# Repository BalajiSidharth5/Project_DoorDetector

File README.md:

## Project_DoorDetector
# DOOR STATE DETECTOR
This project detects whether a door is open or closed using infrared reflection. It runs on two Adafruit HUZZAH32 boards.

# HOW IT WORKS
One HUZZAH32 sits at the door and reads the WWZMDiB 3 wire IR sensor. The sensor reflects IR off the door surface. When the door sits in front of the sensor, IR bounces back and the output reads one state. When the door swings open, the surface moves out of range and the output flips. A trim pot on the sensor sets the trigger distance.
The second HUZZAH32 acts as the receiver. It gets the door state and lights an LED to show open or closed.

# HARDWARE
- 2x Adafruit HUZZAH32
- WWZMDiB 3 wire IR sensor module
- 2x tactile pushbuttons, one on each HUZZAH32
- Status LED on each HUZZAH32, shows whether that board is awake
- LED on the receiver HUZZAH32, shows door open or closed state
- 220 ohm resistors for all LEDs
- 10k ohm resistors for both tactile buttons
- Rechargeable AA battery pack, wired directly to power and ground

# FIRMWARE
Button input is debounced in firmware on both boards.
Both boards run deep sleep to cut power draw. Each board wakes from deep sleep when you press its tactile button. The status LED on each board turns on when that board is awake and off when it drops back into deep sleep. This keeps both boards off when user does not need it. Utilized ESPnow library to communicate data between microcontrollers.

# POWER
The device runs on rechargeable AA cells instead of a lithium ion pack. Power and ground connect directly to the microcontroller with no charge circuit on board. Charging happens outside the device, in a standalone AA charger.

# STATUS
Breadboard prototype complete. PCB layout in progress in KiCad, targeting a compact 3D printed enclosure.

# NEXT STEPS
- Finish PCB layout in KiCad
- Design 3D printed enclosure around the board

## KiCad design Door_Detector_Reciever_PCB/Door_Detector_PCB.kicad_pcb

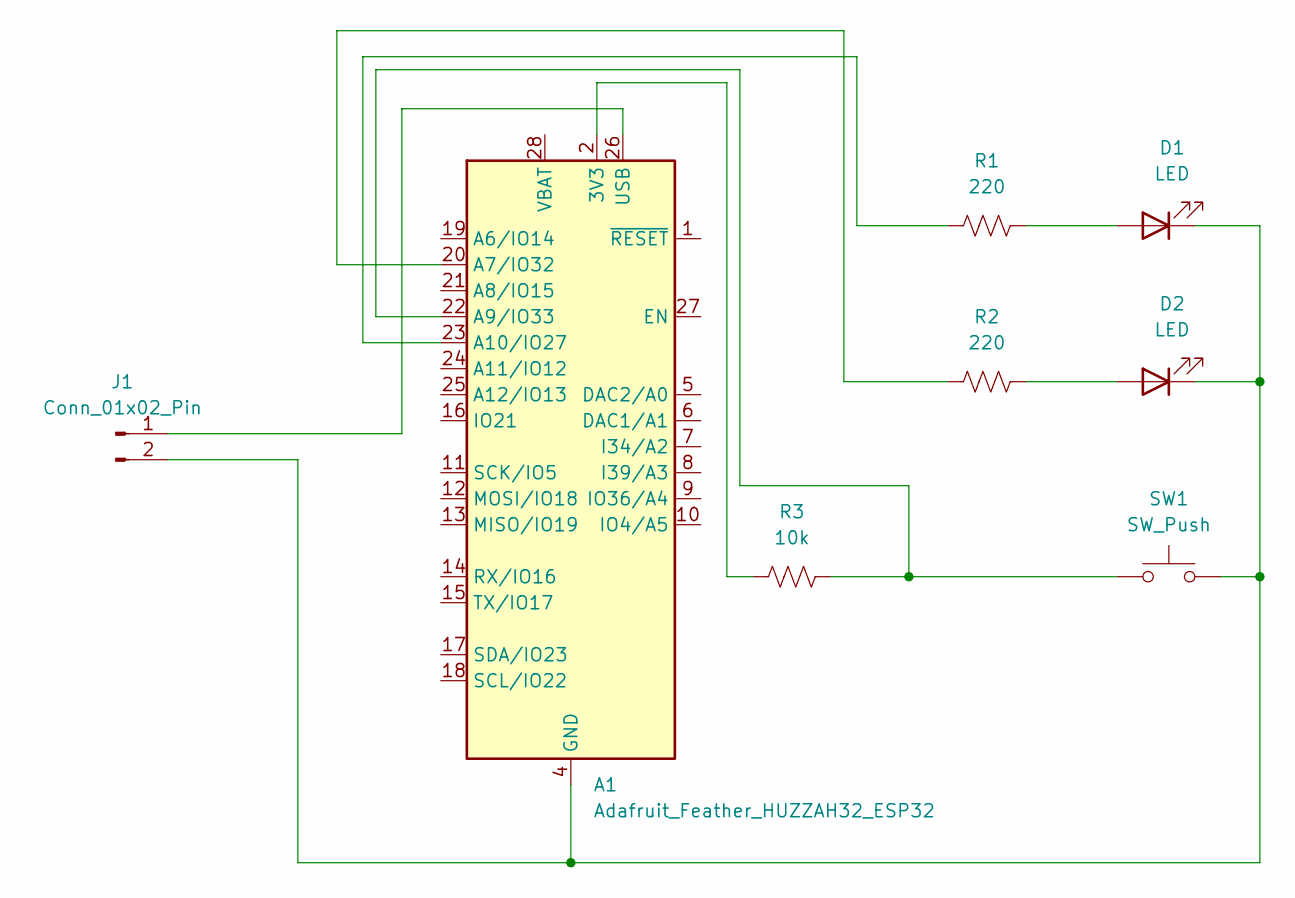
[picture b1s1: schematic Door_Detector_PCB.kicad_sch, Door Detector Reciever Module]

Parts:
A1: Adafruit_Feather_HUZZAH32_ESP32; Adafruit_Feather
D1, D2: LED; LED_D5.0mm
J1: Conn_01x02_Pin; PinHeader_1x02_P2.54mm_Vertical
R1, R2: 220; R_Axial_DIN0207_L6.3mm_D2.5mm_P7.62mm_Horizontal
R3: 10k; R_Axial_DIN0207_L6.3mm_D2.5mm_P7.62mm_Horizontal
SW1: SW_Push; SW_PUSH_6mm

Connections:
unnamed: A1.2 (3V3), R3.1
unnamed: A1.20 (A7/IO32), R2.1
unnamed: A1.22 (A9/IO33), R3.2, SW1.1
unnamed: A1.23 (A10/IO27), R1.1
unnamed: A1.4 (GND), D1.1 (K), D2.1 (K), J1.2, SW1.2
unnamed: A1.26 (USB), J1.1
unnamed: D1.2 (A), R1.2
unnamed: D2.2 (A), R2.2

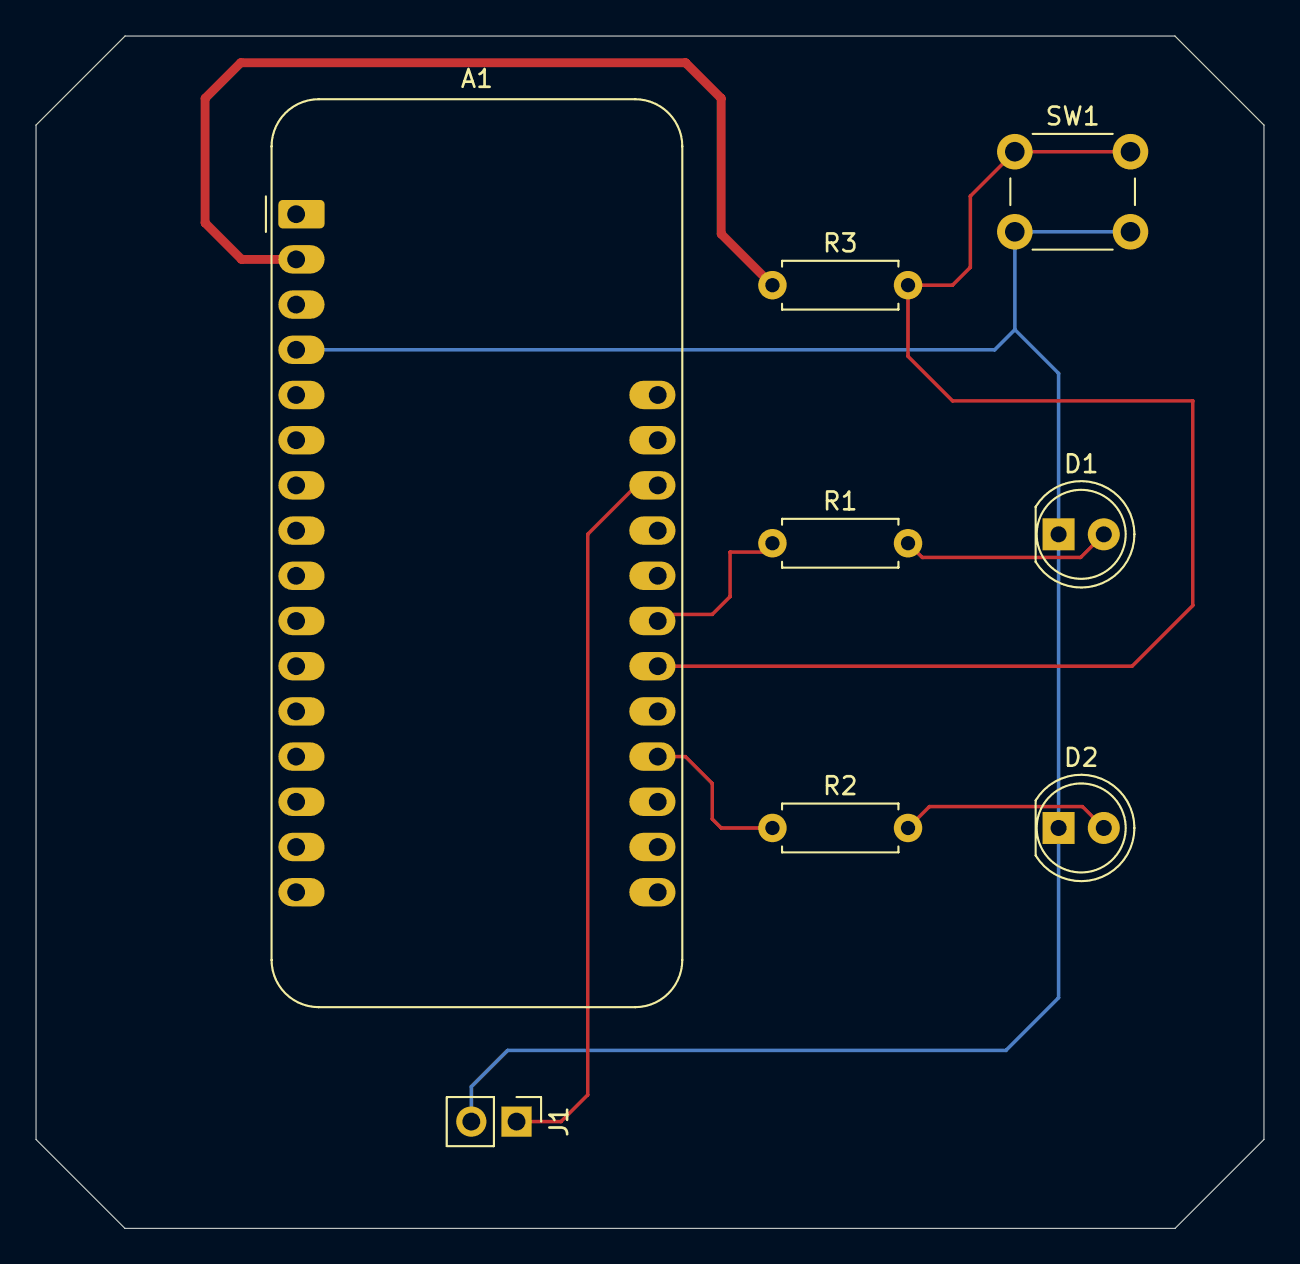
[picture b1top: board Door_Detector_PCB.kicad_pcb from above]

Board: 2 copper layers, 69.0 x 67.0 mm, 8 parts (0 on the bottom side), 8 nets.

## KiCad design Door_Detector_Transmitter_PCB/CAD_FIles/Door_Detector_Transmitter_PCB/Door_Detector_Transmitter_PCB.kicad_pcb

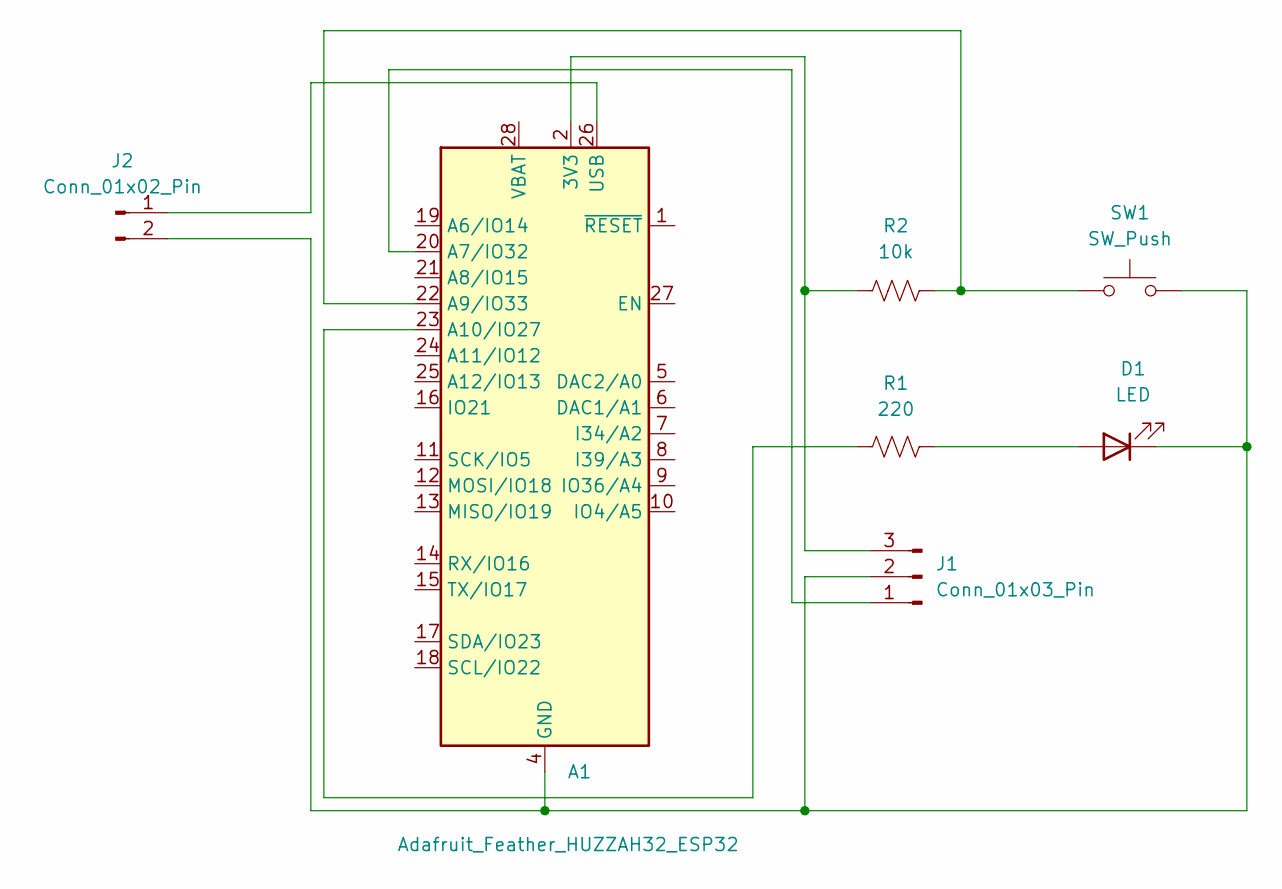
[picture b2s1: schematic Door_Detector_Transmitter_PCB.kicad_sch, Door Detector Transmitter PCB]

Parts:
A1: Adafruit_Feather_HUZZAH32_ESP32; Adafruit_Feather
D1: LED; LED_D5.0mm
J1: Conn_01x03_Pin; PinHeader_1x03_P2.54mm_Vertical
J2: Conn_01x02_Pin; PinHeader_1x02_P2.54mm_Vertical
R1: 220; R_Axial_DIN0207_L6.3mm_D2.5mm_P7.62mm_Horizontal
R2: 10k; R_Axial_DIN0207_L6.3mm_D2.5mm_P7.62mm_Horizontal
SW1: SW_Push; SW_PUSH_6mm

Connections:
unnamed: A1.2 (3V3), J1.3, R2.1
unnamed: A1.20 (A7/IO32), J1.1
unnamed: A1.22 (A9/IO33), R2.2, SW1.1
unnamed: A1.23 (A10/IO27), R1.1
unnamed: A1.4 (GND), D1.1 (K), J1.2, J2.2, SW1.2
unnamed: A1.26 (USB), J2.1
unnamed: D1.2 (A), R1.2

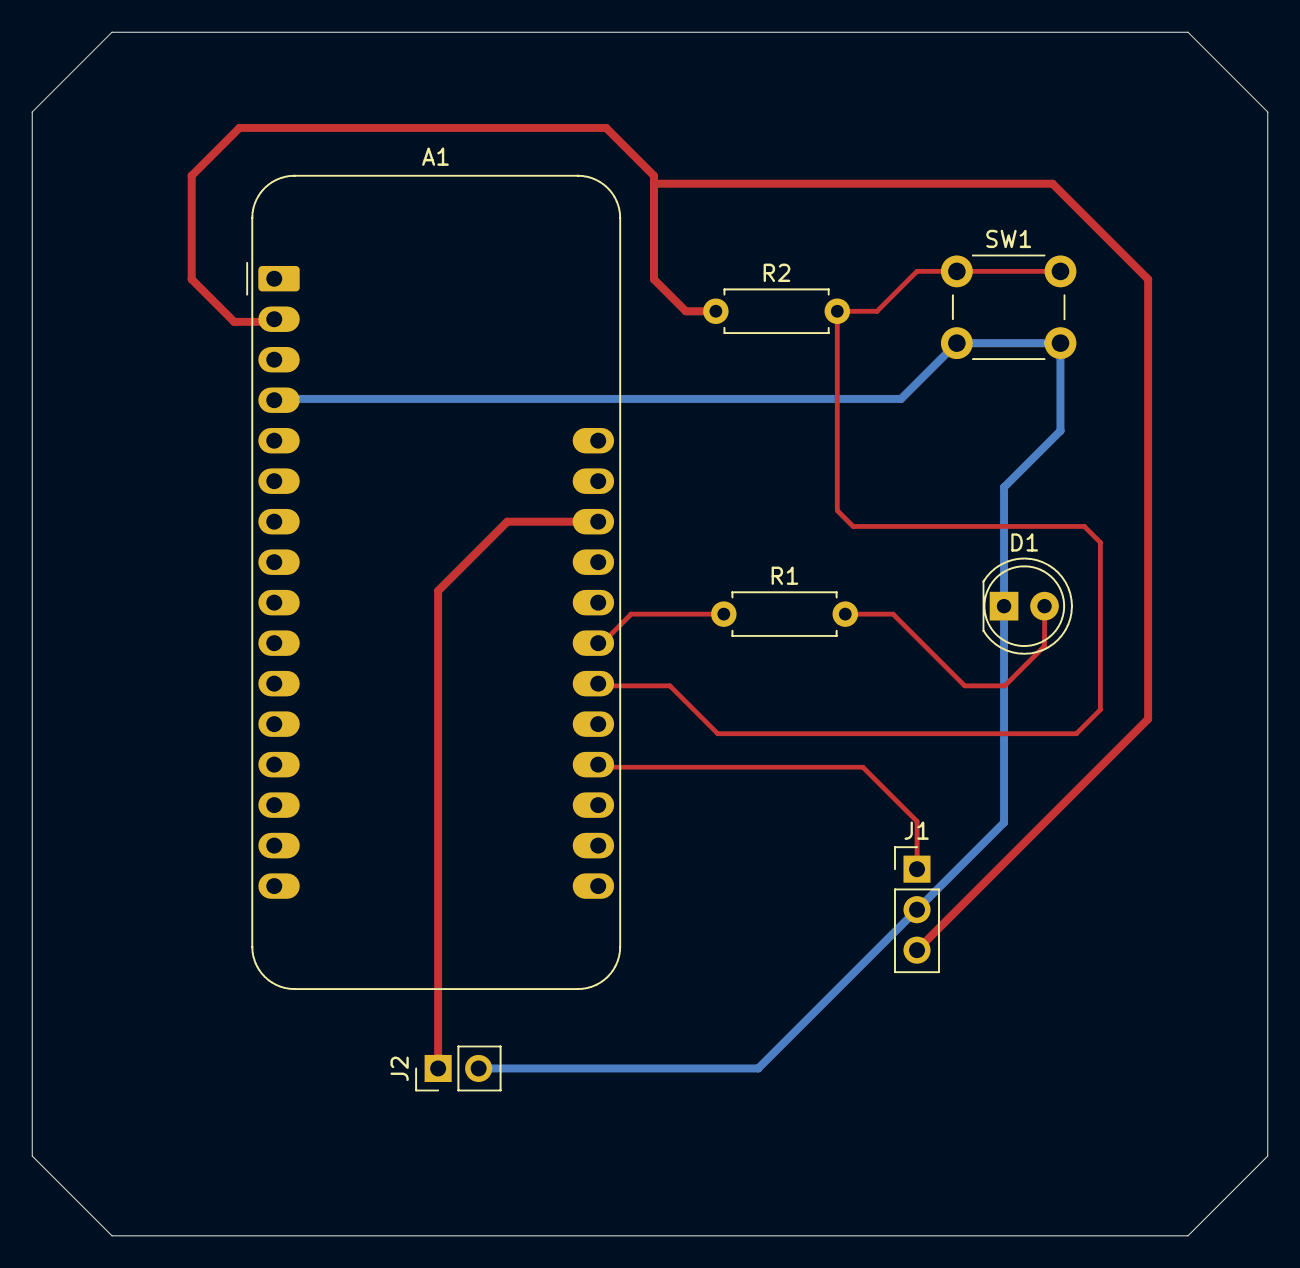
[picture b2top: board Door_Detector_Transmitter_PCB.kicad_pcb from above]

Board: 2 copper layers, 77.5 x 75.5 mm, 7 parts (0 on the bottom side), 7 nets.
